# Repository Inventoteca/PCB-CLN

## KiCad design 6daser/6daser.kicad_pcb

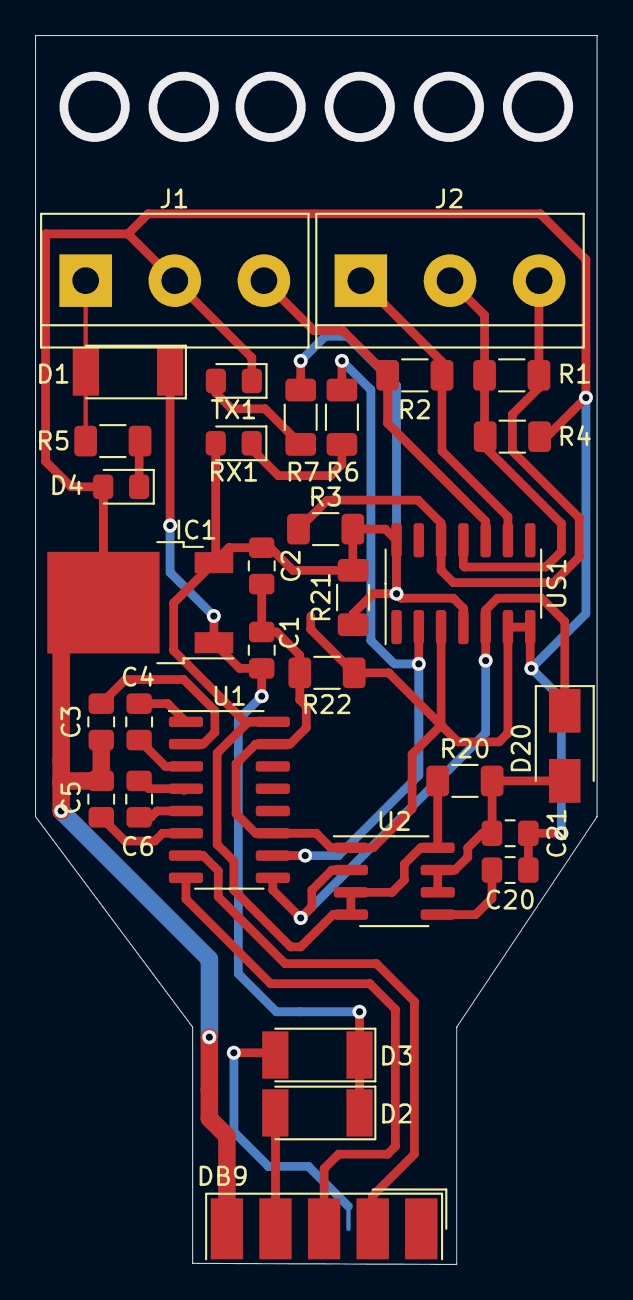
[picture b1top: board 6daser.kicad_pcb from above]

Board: 2 copper layers, 32.0 x 70.0 mm, 32 parts (0 on the bottom side), 25 nets.

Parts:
C1, C2, C3, C4, C5, C6, C20, C21: C_Small; C_0805_2012Metric_Pad1.18x1.45mm_HandSolder
D1, D2, D3: DIODE; D_MELF
D4: DIODE; LED_0805_2012Metric_Pad1.15x1.40mm_HandSolder
D20: DIODE; D_SMA
DB9: DB9_Female; DSUB-9_Female_EdgeMount_P2.77mm
IC1: LM78M05_TO220; TO-252-2
J1, J2: Screw_Terminal_01x03; TerminalBlock_bornier-3_P5.08mm
R1, R2: .; R_1206_3216Metric_Pad1.30x1.75mm_HandSolder
R3, R4, R5, R6, R7, R20, R21, R22: R_Small; R_1206_3216Metric_Pad1.30x1.75mm_HandSolder
RX1: R_Small; LED_0805_2012Metric_Pad1.15x1.40mm_HandSolder
TX1: .; LED_0805_2012Metric_Pad1.15x1.40mm_HandSolder
U1: MAX232; SOIC-16_3.9x9.9mm_P1.27mm
U2: ICE1PCS01; SOIC-8_3.9x4.9mm_P1.27mm
US1: MAX491E; SOIC-14_3.9x8.7mm_P1.27mm

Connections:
Earth: C1.1, C2.2, C3.1, C5.1, C20.2, C21.2, D4.2, DB9.5, IC1.2, J1.2, R4.1, R22.1, R22.2, TX1.1, U1.11, U1.15, U2.1, US1.3, US1.6, US1.7
unnamed: C1.2, D1.1, D2.1, D3.1, IC1.1
unnamed: C2.1, IC1.3, R3.2, R7.1, R20.1, R21.1, R21.2, RX1.2, U1.16, U2.3, U2.4, U2.8, US1.4, US1.14
unnamed: C3.2, U1.2
unnamed: C4.1, U1.1
unnamed: C4.2, U1.3
unnamed: C5.2, U1.6
unnamed: C6.1, U1.4
unnamed: C6.2, U1.5
unnamed: C20.1, U2.5
unnamed: C21.1, D20.2, R20.2, U2.6, U2.7
unnamed: D1.2, J1.1, R5.2
unnamed: D2.2, DB9.4
unnamed: D3.2, DB9.7
unnamed: D4.1, R5.1
unnamed: D20.1, U1.9, U2.2, US1.5
unnamed: DB9.2, U1.7
unnamed: DB9.3, U1.8
unnamed: J1.3, R2.1, US1.10
unnamed: J2.1, R2.2, US1.9
unnamed: J2.2, R1.1, R4.2, US1.11
unnamed: J2.3, R1.2, R3.1, US1.12
unnamed: R6.1, RX1.1
unnamed: R6.2, U1.10, US1.2
unnamed: R7.2, TX1.2

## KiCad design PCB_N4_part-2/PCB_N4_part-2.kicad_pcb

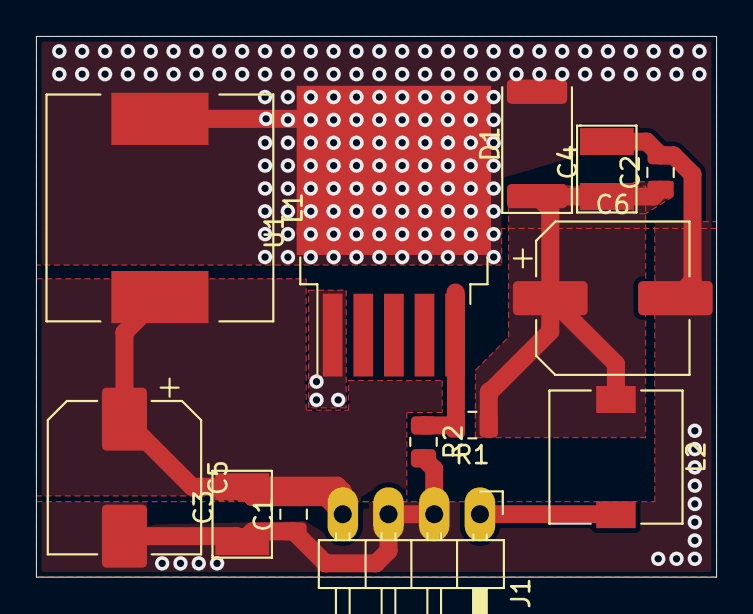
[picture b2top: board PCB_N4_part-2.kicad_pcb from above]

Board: 2 copper layers, 37.8 x 30.0 mm, 13 parts (0 on the bottom side), 6 nets.

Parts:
C1, C2: C_Small; C_0805_2012Metric
C3, C4: C_Small; C_1.5-4.5mm
C5: CP; CP_Elec_8x10
C6: CP; CP_Elec_8x11.9
D1: DIODE; D_2512_6332Metric
J1: Conn_01x04; PinHeader_1x04_P2.54mm_Horizontal
L1: INDUCTOR; L_12x12mm_H8mm
L2: INDUCTOR; L_7.3x7.3_H4.5
R1, R2: R_Small; R_0805_2012Metric
U1: xl6009e1; TO-263-5_TabPin3

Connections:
Earth: C1.1, C2.2, C3.1, C4.2, C5.2, C6.2, J1.2, J1.3, R2.2, U1.1
GND: D1.2, L1.1, U1.3
unnamed: C1.2, C3.2, C5.1, J1.1, L1.2
unnamed: C2.1, C4.1, C6.1, D1.1, L2.1, R1.1
unnamed: J1.4, L2.2
unnamed: R1.2, R2.1, U1.5
